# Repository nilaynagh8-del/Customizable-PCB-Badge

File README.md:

# Customizable PCB-Badge
A customizable PCB badge with built in NFC & games!

# Features
- LED Matrix for fun games like flappy bird or pong
- E-ink display module for displaying ID information
- NFC tag for haring info like websites, etc.
- where the NFC tag directs you to can be changed on you're computer through a USB-C connection
- Fun copper and silkscreen art
- 16 broken out GPIO pins
- 16MB of flash storage for the rp2040
- power only needed when playing games or changing the image on the E-ink display
---
# How to Use
| Mode (long-press SW4 to cycle) | What happens |
|---|---|
| 1. **Flappy** | Flappy-bird on the LED grid. SW3 = flap, SW4 = restart. Speeds up as you score. |
| 2. **Pong** | 2-player pong, first to 5. SW3 = left paddle, SW4 = right paddle. |
| 3. **NFC** | Pick one of 3 payloads with SW3 (URL / text / vCard), write it to the ST25DV tag with SW4. Green frame = tag present, red = not detected. Green sweep = write verified OK. |
| 4. **Demo** | Rainbow across the whole grid. |

SW2 toggles the 6 THT LEDs at any time, in any mode – it's wired straight
to GPIO13.

The NFC tag behaves like a normal Type-5 NDEF tag: after a write, tapping it to
a phone opens the URL, shows the text, or offers the contact card.

**Customizing the NFC payloads**

Edit the three strings near the top of `badge-firmware.ino`:

```cpp
static const char *NFC_PAYLOAD_URL   = "https://hackclub.com";
static const char *NFC_PAYLOAD_TEXT  = "Hello to whoever taps this badge!";
static const char *NFC_PAYLOAD_VCARD = "BEGIN:VCARD\nVERSION:3.0\nFN:YOUR NAME...";
```

URI prefixes are auto-detected (`https://`, `http://www.`, `tel:`, `mailto:` …)
and encoded compactly per the NDEF spec. Writes are verified by read-back; the
password session re-opens between attempts if the first write fails. Firmware
size per payload is capped at 254 bytes (TLV short form) but the payload
themselves are clamped to 200 bytes each — plenty for a URL, a message, and a
contact card on the 512-byte ST25DV04K.
# Designing the PCB
the PCB is pretty compact and tightly packed together with many components, which forced me to make this PCB 6 layers. I used 2 GND planes, one on the top layer and another on the bottom. For the NFC antenna I used a plugin to generate me one with copper wire routing to make it part of the PCB itself so it doesn't require an external antenna. here are some photos of the design below.

_Main MCU Components_

_LEDs and buttons for games_

_E-ink Display_

_NFC tag components_

_LED for fun lighting on the front_

_Final PCB Design_

_PCB front and back_

# Software
The software of this device is pretty simple all you have to do is hold the BOOTSEL button on the board and drop the the [Badge-firmware.ino.uf2](https://github.com/nilaynagh8-del/Customizable-PCB-Badge/blob/main/badge-uf2/badge-firmware.ino.uf2) onto the device. You will then be able to upload you're ID and play games etc.

---
# BOM
|#Part       |#Price          |
|------------|----------------|
| **1x [rp2040](https://www.digikey.com/en/products/detail/raspberry-pi/SC0914(13)/14306010)**     | $0.76     |
| **1x [W25Q128JVS](https://www.digikey.com/en/products/detail/winbond-electronics/W25Q128JVSIQ/5803943)** | $5.99   |
| **1x [USB-C 2.0 receptacle](https://www.digikey.com/en/products/detail/adam-tech/USB-C20-S-RA-CS16A-BK-TR/25701126?gclsrc=aw.ds&gad_source=1&gad_campaignid=20678579980&gbraid=0AAAAADrbLlhqkQkBmy0GhcLsBGkQxSWwA&gclid=Cj0KCQjwrvHWBhDKARIsABmp7h3_4yny3H3xYeCTKnwiGQ5gFquwQlYKCZFCwDuY89yn7uL39px1PEEaAn94EALw_wcB)**    | $0.74  |
| **50x[ SK6812MINI LEDS](https://keeb.io/products/sk-6812-mini-e-rgb-leds-12-pack?srsltid=AYCX9vJHpHxhBnKpgdmcaYFWbcuSSWfHne0xMPR1KBHh8PzNO1_xWtn2)**    | $11.98    |
| **1x [ST25DV04K-IER8C3](https://www.digikey.com/en/products/detail/stmicroelectronics/ST25DV04K-IER6T3/6691418?gclsrc=aw.ds&gad_source=1&gad_campaignid=24216345527&gbraid=0AAAAADrbLli4CTTxePQYnJ5C6afwPKjL2&gclid=Cj0KCQjwrvHWBhDKARIsABmp7h1KdPLxHsMZuuaStQSl7R8vMIvJZ-5TIm2zWNzuZK7JSieiJ8zBqwcaAgxCEALw_wcB)**    | $1.10  |
| **6x [5mm THT LED](https://www.digikey.com/en/products/detail/rohm-semiconductor/SLR-56VC3F/636991?gclsrc=aw.ds&gad_source=1&gad_campaignid=20747733577&gbraid=0AAAAADrbLlibUioa_7C1IycEGCDz0hbTg&gclid=Cj0KCQjwrvHWBhDKARIsABmp7h10cfeflSGWLhXNBAp4XJWPd0hMV-nY00NDLkXkriuKhSCe2A7cvd8aAgY_EALw_wcB)**    | $3.30 |
| **3x [PTS645Sx43SMTR92 Switches](https://www.digikey.com/en/products/detail/wec/PTS645SK43SMTR92LFS/27533114?gclsrc=aw.ds&gad_source=4&gad_campaignid=23033451739&gbraid=0AAAAADrbLlh-8VarSu1z8cuQMuamoVxbl&gclid=Cj0KCQjwrvHWBhDKARIsABmp7h1Eo3e9FToyXaLy61q9kBlwUjuhkKtIDu0mgIWiZOV7CFqwBuzqiGIaAisyEALw_wcB)**    | $1.08|
| **1x [KMR2 switch](https://www.digikey.com/en/products/detail/c-k/KMR221G-LFS/550472?gclsrc=aw.ds&gad_source=1&gad_campaignid=20243136172&gbraid=0AAAAADrbLlj0U90TogABbZu38P156Ls3i&gclid=Cj0KCQjwrvHWBhDKARIsABmp7h1JYl6i5VjO5_h80ofNfqxeWJDCjkMDnMpPE0zijLod7d3QZ9AqAecaAiA4EALw_wcB)**    | $0.67 |
| **14x[ 0402 0.1uf capacitors](https://www.digikey.com/en/products/detail/murata-electronics/GRM155C81E104KA12D/6605993?gclsrc=aw.ds&gad_source=4&gad_campaignid=20509818233&gbraid=0AAAAADrbLlis9pHS9r0m2ZhlQP6IInvQA&gclid=Cj0KCQjwrvHWBhDKARIsABmp7h07aUFT4WDWhllQ61V_xpzCK5QXNSUuiS_rN4leZ1_dai8NjVI8rQsaAgjsEALw_wcB)**    | $1.40    |
| **3x [0603 10uf capacitors](https://www.digikey.com/en/products/detail/murata-electronics/GRT188R60J106ME13J/13904886?gclsrc=aw.ds&gad_source=1&gad_campaignid=20509818233&gbraid=0AAAAADrbLlhW4hUYZwqaRXxXOI1TvvnLC&gclid=Cj0KCQjwrvHWBhDKARIsABmp7h1m43mU9iI4nKG-fnOtnU_kfMY8bhoRzj5BhlG1TujyhKJdcvszKPgaAnMzEALw_wcB)**    | $0.63 |
| **4x [0402 15pf  capacitors](https://www.digikey.com/en/products/detail/yageo/CC0402FRNPO9BN150/5195051)**    | $0.52    |
| **1x [NCP1117ST33T3G](https://www.digikey.com/en/products/detail/onsemi/NCP1117ST33T3G/1749063)**    | $0.65    |
| **2x [5.1k 0402 resistors](https://www.digikey.com/en/products/detail/yageo/RC0402FR-075K1L/726624)**    | $0.20    |
| **2x [27 ohm 0402 resistors](https://www.digikey.com/en/products/detail/yageo/RC0402FR-0727RL/5280946)**    | $0.20    |
| **2x [1k  0402 resistors](https://www.digikey.com/en/products/detail/yageo/RC0402FR-071KL/726513)**    | $0.20    |
| **1x [10k  0402 resistors](https://www.digikey.com/en/products/detail/vishay-dale/RCA040210K0FKED/4946751)**    | $0.11 |
| **2x [4.7k  0402 resistors](https://www.digikey.com/en/products/detail/yageo/RC0402JR-074K7L/726477)**    | $0.10 |
| **1x [470 ohm  0402 resistors](https://www.digikey.com/en/products/detail/yageo/RC0402FR-07470RP/4935284)**    | $0.11 |
| **1x [E-ink Display]([https://www.digikey.com/en/products/detail/yageo/RC0402FR-07470RP/4935284](https://www.amazon.com/2-13inch-Display-HAT-Two-Color-Raspberry/dp/B07Z1WYRQH/ref=sr_1_11?dib=eyJ2IjoiMSJ9.gn6VLudgU0EyGmCtn6ouiN-En84h8hGdmjGuK1-66Xws_QcTkqImKZ7qe8NUiArwhwJk9JiOutgNeIz5cPmB0ZbkMG4yFjYDLpp9DKV0toxfU2H8bp0QUR760J-i1QKpJPyA7FF0PKqdo7Qt2GiVY_zAQcLqV49bpBDsulBlm3EtA--w29KZabezZMWkaSrQsFDFI53NmnQb6Gi7EZZHmbqM53_gEwxUkAk3kj63XW4.dg_95URBlxNDf7plGtIUSDxYDGLFnQ1UMweHCZRH_n8&dib_tag=se&keywords=e-ink+display&qid=1792900939&sr=8-11))**    | $23.03 |
| **Total Price of Parts (excluding PCB)**  | $52.77 |

# Disclaimers & Credits
This project is open source. If anything you make out of this does not work or has any issues, I sincerely apologize, but at the end of the day that's on you. Big shout out to Hack Club for giving me the opportunity to make this project. I would also like to thank **Kai Pereira**, as my project is heavily inspired his PCB badge in many ways.

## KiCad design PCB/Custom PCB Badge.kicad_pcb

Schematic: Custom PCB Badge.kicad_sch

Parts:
C1, C2, C3, C4, C5, C6, C7, C8, C9, C10, C11, C12, C17: 0.1uf; C_0402_1005Metric_Pad0.74x0.62mm_HandSolder
C13, C14, C18: 10uf; C_0603_1608Metric_Pad1.08x0.95mm_HandSolder
C15, C16: 15pf; C_0402_1005Metric_Pad0.74x0.62mm_HandSolder
J1: USB_C_Receptacle_USB2.0_14P; USB_C_Receptacle_HRO_TYPE-C-31-M-12
J3: Conn_01x15_MountingPin; PinHeader_1x15_P2.54mm_Vertical
J8: Conn_01x11_MountingPin; PinHeader_1x11_P2.54mm_Vertical
R1: 5.1K; R_0402_1005Metric_Pad0.72x0.64mm_HandSolder
R2: 5.1k; R_0402_1005Metric_Pad0.72x0.64mm_HandSolder
R3, R4: 27; R_0402_1005Metric_Pad0.72x0.64mm_HandSolder
R5, R6: 1k; R_0402_1005Metric_Pad0.72x0.64mm_HandSolder
R7: 10k; R_0402_1005Metric_Pad0.72x0.64mm_HandSolder
SW1: SW_Push; SW_Push_1P1T_NO_CK_KMR2
U1: RP2040; QFN-56-1EP_7x7mm_P0.4mm_EP3.2x3.2mm
U2: NCP1117-3.3_SOT223; SOT-223-3_TabPin2
U3: W25Q128JVS; SOIC-8_5.3x5.3mm_P1.27mm
Y1: 12mhz; Crystal_SMD_3225-4Pin_3.2x2.5mm_HandSoldering

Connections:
+1V1: C10.1, C11.1, C12.1, U1.43 (ADC_AVDD), U1.48 (USB_VDD)
+3V3: C1.1, C2.1, C3.1, C4.1, C5.1, C6.1, C7.1, C8.1, C9.1, C14.1, C17.1, J3.5, J8.5, R7.1, U1.1 (IOVDD), U1.10 (IOVDD), U1.22 (IOVDD), U1.23 (DVDD), U1.33 (IOVDD), U1.42 (IOVDD), U1.44 (VREG_VIN), U1.45 (VREG_VOUT), U1.49 (IOVDD), U1.50 (DVDD), U2.2 (VO), U3.8 (VCC); also elsewhere on the board
+5V: C13.1, C18.1, J1.A4 (VBUS), J1.A9 (VBUS), J1.B4 (VBUS), J1.B9 (VBUS), J3.1, J8.1, U2.3 (VI)
/d+: J1.A6 (D+), J1.B6 (D+), R3.1
/d-: J1.A7 (D-), J1.B7 (D-), R4.1
/xin: C16.2, U1.20 (XIN), Y1.3
/xout: R5.2, U1.21 (XOUT)
GND: C1.2, C2.2, C3.2, C4.2, C5.2, C6.2, C7.2, C8.2, C9.2, C10.2, C11.2, C12.2, C13.2, C14.2, C15.1, C16.1, C17.2, C18.2, J1.A1 (GND), J1.A12 (GND), J1.B1 (GND), J1.B12 (GND), J1.SH (SHIELD), J3.3, J3.8, J3.13, J8.3, J8.8, J8.10, R1.2, R2.1, SW1.1, U1.19 (TESTEN), U1.57 (GND), U2.1 (GND), U3.4 (GND), Y1.2 (G), Y1.4 (G); also elsewhere on the board
GPIO0: J3.2, U1.2 (GPIO0)
GPIO1: J3.4, U1.3 (GPIO1)
GPIO2: J3.6, U1.4 (GPIO2)
GPIO3: J3.7, U1.5 (GPIO3)
GPIO4: J3.9, U1.6 (GPIO4)
GPIO5: J3.10, U1.7 (GPIO5)
GPIO6: J3.11, U1.8 (GPIO6)
GPIO7: J3.12, U1.9 (GPIO7)
GPIO8: J3.14, U1.11 (GPIO8)
GPIO9: J3.15, U1.12 (GPIO9)
GPIO10: U1.13 (GPIO10); also elsewhere on the board
GPIO11: U1.14 (GPIO11); also elsewhere on the board
GPIO12: U1.15 (GPIO12); also elsewhere on the board
GPIO13: U1.16 (GPIO13); also elsewhere on the board
GPIO14: J8.4, U1.17 (GPIO14)
GPIO15: J8.6, U1.18 (GPIO15)
GPIO16: J8.7, U1.27 (GPIO16)
GPIO17: J8.9, U1.28 (GPIO17)
GPIO18: J8.11, U1.29 (GPIO18)
GPIO19: J8.2, U1.30 (GPIO19)
GPIO20: U1.31 (GPIO20); also elsewhere on the board
GPIO21: U1.32 (GPIO21); also elsewhere on the board
GPIO22: U1.34 (GPIO22); also elsewhere on the board
GPIO23: U1.35 (GPIO23); also elsewhere on the board
GPIO24: U1.36 (GPIO24); also elsewhere on the board
GPIO25: U1.37 (GPIO25); also elsewhere on the board
GPIO26: U1.38 (GPIO26/ADC0); also elsewhere on the board
GPIO27: U1.39 (GPIO27/ADC1); also elsewhere on the board
GPIO28: U1.40 (GPIO28/ADC2); also elsewhere on the board
GPIO29: U1.41 (GPIO29/ADC3); also elsewhere on the board
unnamed: C15.2, R5.1, Y1.1
unnamed: J1.A5 (CC1), R1.1
unnamed: J1.B5 (CC2), R2.2
unnamed: R6.1, SW1.2
unnamed: R3.2, U1.46 (USB_DM)
unnamed: R4.2, U1.47 (USB_DP)
QSPISS: R6.2, R7.2, U1.56 (~QSPI_SS), U3.1 (~CS)
QSPI_SCLK: U1.52 (QSPI_SCLK), U3.6 (CLK)
QSPI_SD0: U1.53 (QSPI_SD0), U3.5 (DI/IO_{0})
QSPI_SD1: U1.55 (QSPI_SD1), U3.2 (DO/IO_{1})
QSPI_SD2: U1.54 (QSPI_SD2), U3.3 (~WP/IO_{2})
QSPI_SD3: U1.51 (QSPI_SD3), U3.7 (~HOLD/~RESET/IO_{3})
RUN: U1.26 (RUN)

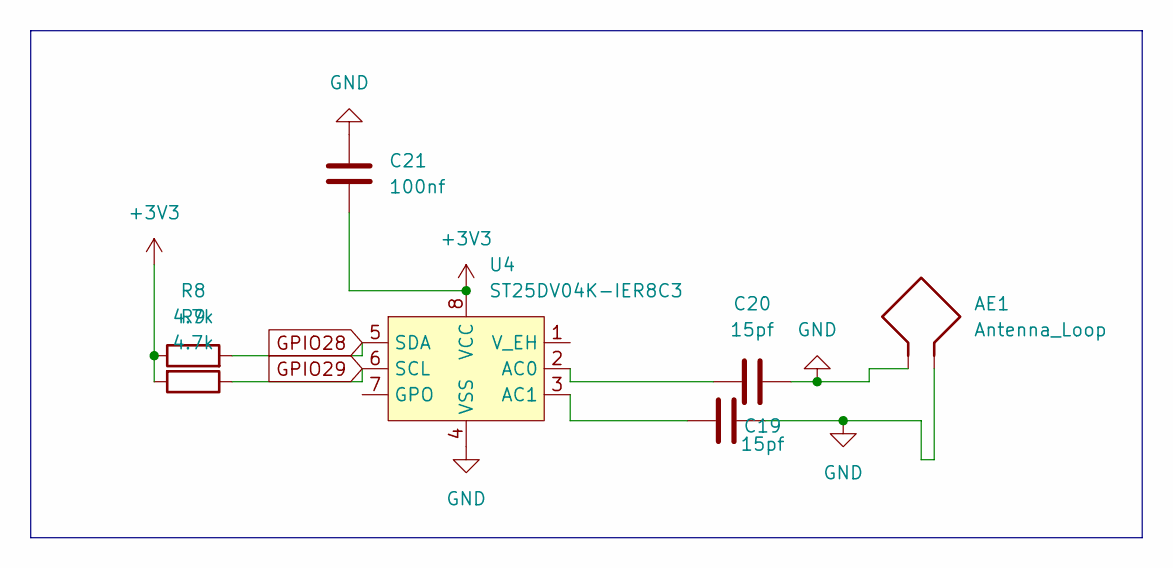
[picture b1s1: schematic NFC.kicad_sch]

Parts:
AE1: Antenna_Loop; PinHeader_1x02_P2.54mm_Vertical_SMD_Pin1Left
C19, C20: 15pf; C_0402_1005Metric_Pad0.74x0.62mm_HandSolder
C21: 100nf; C_0402_1005Metric_Pad0.74x0.62mm_HandSolder
R8, R9: 4.7k; R_0402_1005Metric_Pad0.72x0.64mm_HandSolder
U4: ST25DV04K-IER8C3; DFN-8-1EP_3x2mm_P0.5mm_EP1.36x1.46mm

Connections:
+3V3: C21.1, R8.1, R9.2, U4.8 (VCC); also elsewhere on the board
GND: AE1.1, AE1.2, C19.2, C20.2, C21.2, U4.4 (VSS); also elsewhere on the board
GPIO28: R8.2, U4.5 (SDA); also elsewhere on the board
GPIO29: R9.1, U4.6 (SCL); also elsewhere on the board
unnamed: C20.1, U4.2 (AC0)
unnamed: C19.1, U4.3 (AC1)

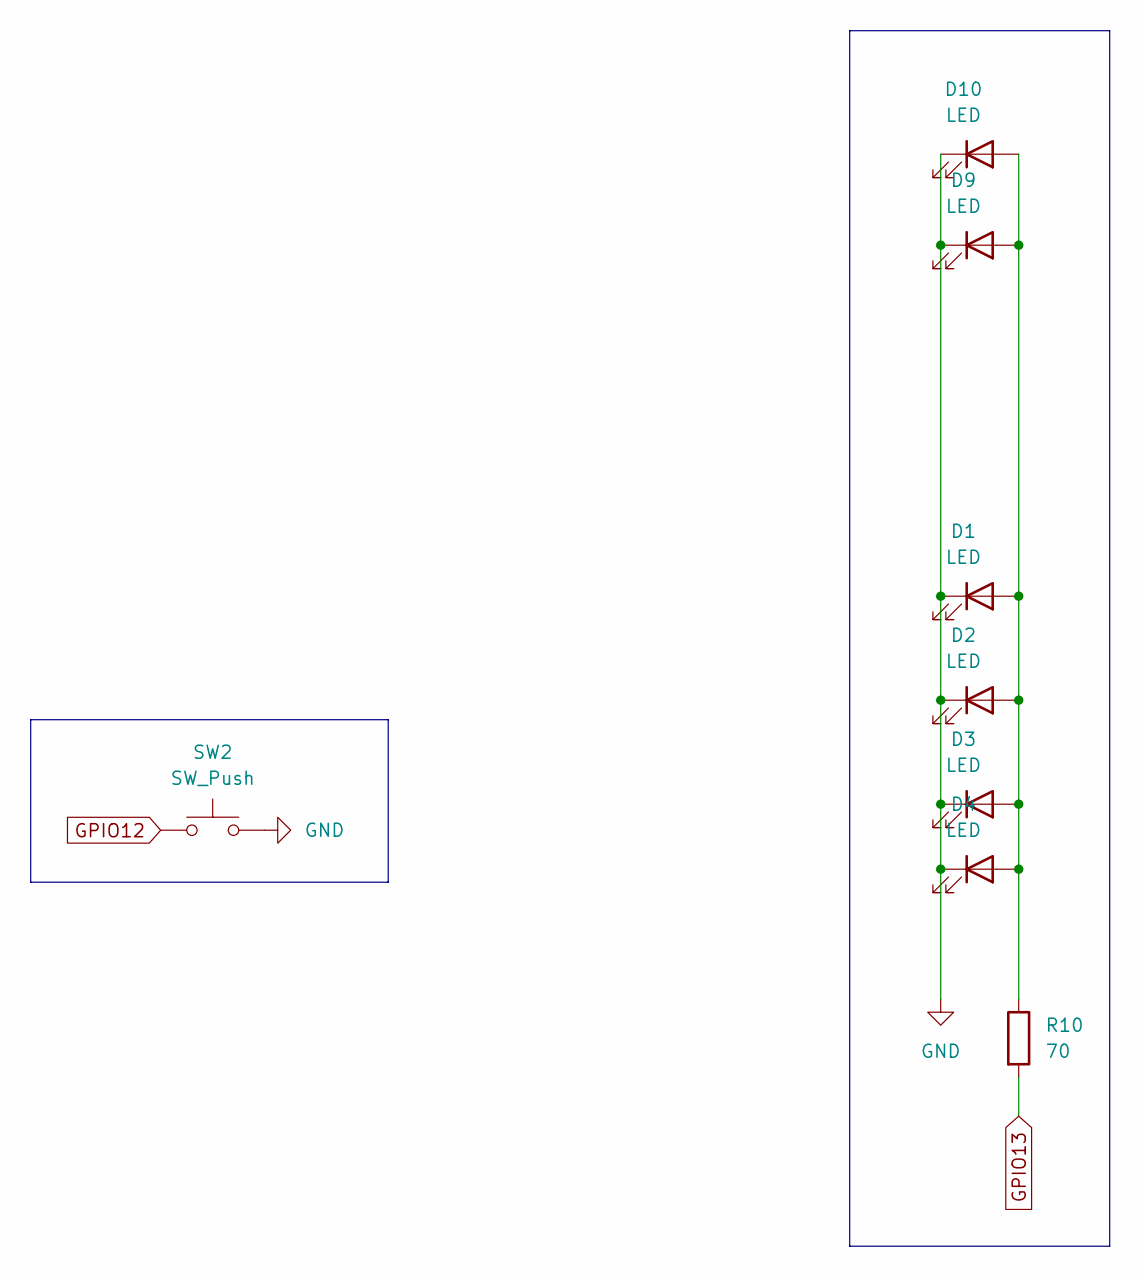
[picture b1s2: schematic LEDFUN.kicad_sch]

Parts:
D1, D2, D3, D4, D9, D10: LED; LED_D5.0mm
R10: 70; R_0402_1005Metric_Pad0.72x0.64mm_HandSolder
SW2: SW_Push; SW_SPST_PTS645Sx43SMTR92

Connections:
GND: D1.1 (K), D2.1 (K), D3.1 (K), D4.1 (K), D9.1 (K), D10.1 (K), SW2.2; also elsewhere on the board
GPIO12: SW2.1; also elsewhere on the board
GPIO13: R10.2; also elsewhere on the board
unnamed: D1.2 (A), D2.2 (A), D3.2 (A), D4.2 (A), D9.2 (A), D10.2 (A), R10.1

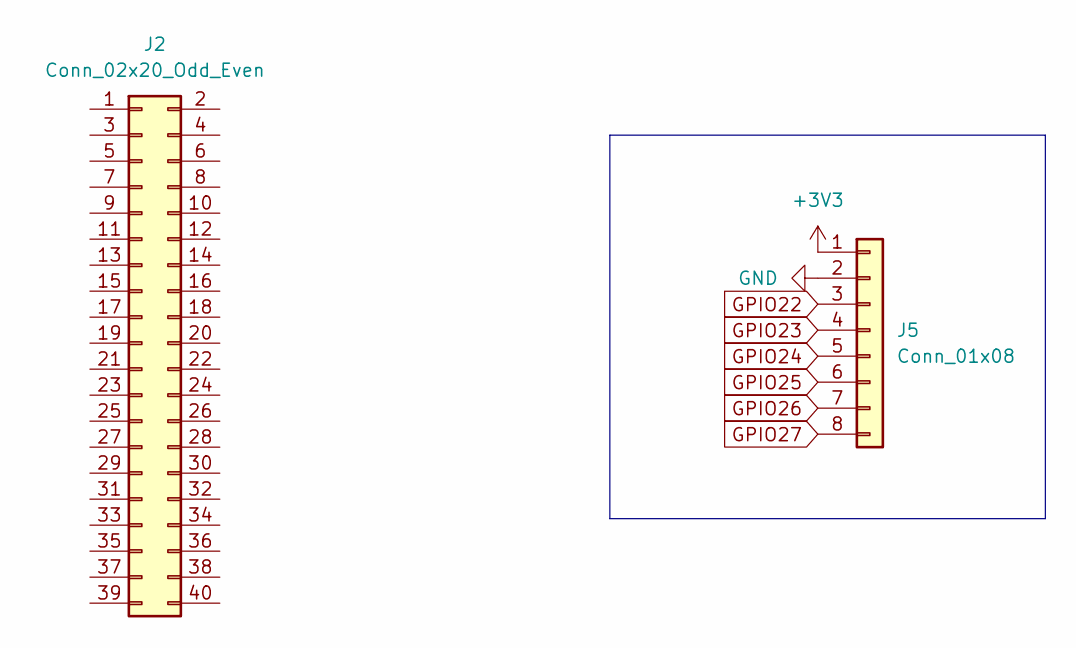
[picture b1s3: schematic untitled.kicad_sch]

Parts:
J2: Conn_02x20_Odd_Even; PinHeader_2x20_P2.54mm_Vertical
J5: Conn_01x08; PinHeader_1x08_P2.54mm_Vertical

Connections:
+3V3: J5.1; also elsewhere on the board
GND: J5.2; also elsewhere on the board
GPIO22: J5.3; also elsewhere on the board
GPIO23: J5.4; also elsewhere on the board
GPIO24: J5.5; also elsewhere on the board
GPIO25: J5.6; also elsewhere on the board
GPIO26: J5.7; also elsewhere on the board
GPIO27: J5.8; also elsewhere on the board

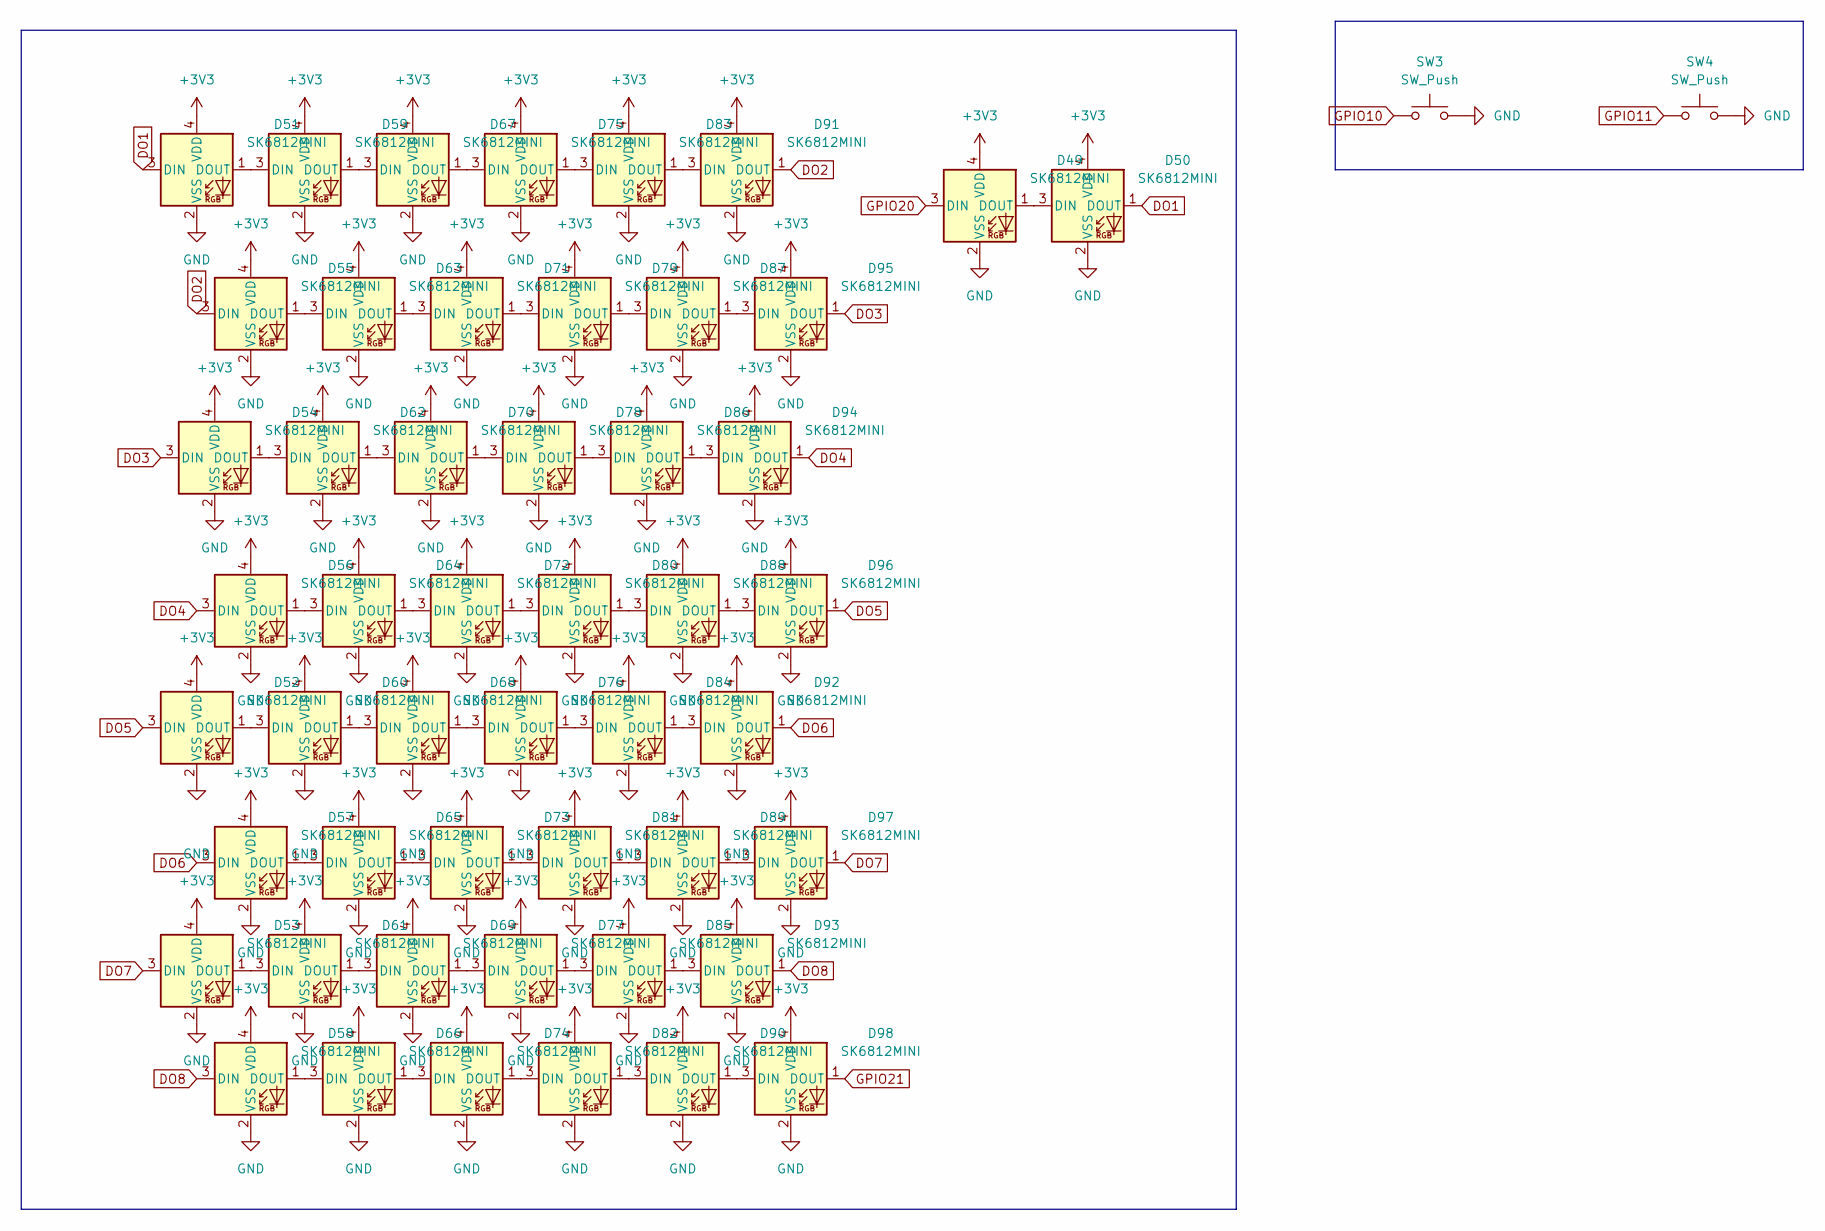
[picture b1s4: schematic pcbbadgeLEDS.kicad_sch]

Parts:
D49, D50, D51, D52, D53, D54, D55, D56, D57, D58, D59, D60, D61, D62, D63, D64, D65, D66, D67, D68, D69, D70, D71, D72, D73, D74, D75, D76, D77, D78, D79, D80, D81, D82, D83, D84, D85, D86, D87, D88, D89, D90, D91, D92, D93, D94, D95, D96, D97, D98: SK6812MINI; LED_SK6812MINI_PLCC4_3.5x3.5mm_P1.75mm
SW3, SW4: SW_Push; SW_SPST_PTS645Sx43SMTR92

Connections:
+3V3: D49.4 (VDD), D50.4 (VDD), D51.4 (VDD), D52.4 (VDD), D53.4 (VDD), D54.4 (VDD), D55.4 (VDD), D56.4 (VDD), D57.4 (VDD), D58.4 (VDD), D59.4 (VDD), D60.4 (VDD), D61.4 (VDD), D62.4 (VDD), D63.4 (VDD), D64.4 (VDD), D65.4 (VDD), D66.4 (VDD), D67.4 (VDD), D68.4 (VDD), D69.4 (VDD), D70.4 (VDD), D71.4 (VDD), D72.4 (VDD), D73.4 (VDD), D74.4 (VDD), D75.4 (VDD), D76.4 (VDD), D77.4 (VDD), D78.4 (VDD), D79.4 (VDD), D80.4 (VDD), D81.4 (VDD), D82.4 (VDD), D83.4 (VDD), D84.4 (VDD), D85.4 (VDD), D86.4 (VDD), D87.4 (VDD), D88.4 (VDD), D89.4 (VDD), D90.4 (VDD), D91.4 (VDD), D92.4 (VDD), D93.4 (VDD), D94.4 (VDD), D95.4 (VDD), D96.4 (VDD), D97.4 (VDD), D98.4 (VDD); also elsewhere on the board
DO1: D50.1 (DOUT), D51.3 (DIN)
DO2: D55.3 (DIN), D91.1 (DOUT)
DO3: D54.3 (DIN), D95.1 (DOUT)
DO4: D56.3 (DIN), D94.1 (DOUT)
DO5: D52.3 (DIN), D96.1 (DOUT)
DO6: D57.3 (DIN), D92.1 (DOUT)
DO7: D53.3 (DIN), D97.1 (DOUT)
DO8: D58.3 (DIN), D93.1 (DOUT)
GND: D49.2 (VSS), D50.2 (VSS), D51.2 (VSS), D52.2 (VSS), D53.2 (VSS), D54.2 (VSS), D55.2 (VSS), D56.2 (VSS), D57.2 (VSS), D58.2 (VSS), D59.2 (VSS), D60.2 (VSS), D61.2 (VSS), D62.2 (VSS), D63.2 (VSS), D64.2 (VSS), D65.2 (VSS), D66.2 (VSS), D67.2 (VSS), D68.2 (VSS), D69.2 (VSS), D70.2 (VSS), D71.2 (VSS), D72.2 (VSS), D73.2 (VSS), D74.2 (VSS), D75.2 (VSS), D76.2 (VSS), D77.2 (VSS), D78.2 (VSS), D79.2 (VSS), D80.2 (VSS), D81.2 (VSS), D82.2 (VSS), D83.2 (VSS), D84.2 (VSS), D85.2 (VSS), D86.2 (VSS), D87.2 (VSS), D88.2 (VSS), D89.2 (VSS), D90.2 (VSS), D91.2 (VSS), D92.2 (VSS), D93.2 (VSS), D94.2 (VSS), D95.2 (VSS), D96.2 (VSS), D97.2 (VSS), D98.2 (VSS), SW3.2, SW4.2; also elsewhere on the board
GPIO10: SW3.1; also elsewhere on the board
GPIO11: SW4.1; also elsewhere on the board
GPIO20: D49.3 (DIN); also elsewhere on the board
GPIO21: D98.1 (DOUT); also elsewhere on the board
unnamed: D49.1 (DOUT), D50.3 (DIN)
unnamed: D51.1 (DOUT), D59.3 (DIN)
unnamed: D52.1 (DOUT), D60.3 (DIN)
unnamed: D53.1 (DOUT), D61.3 (DIN)
unnamed: D54.1 (DOUT), D62.3 (DIN)
unnamed: D55.1 (DOUT), D63.3 (DIN)
unnamed: D56.1 (DOUT), D64.3 (DIN)
unnamed: D57.1 (DOUT), D65.3 (DIN)
unnamed: D58.1 (DOUT), D66.3 (DIN)
unnamed: D59.1 (DOUT), D67.3 (DIN)
unnamed: D60.1 (DOUT), D68.3 (DIN)
unnamed: D61.1 (DOUT), D69.3 (DIN)
unnamed: D62.1 (DOUT), D70.3 (DIN)
unnamed: D63.1 (DOUT), D71.3 (DIN)
unnamed: D64.1 (DOUT), D72.3 (DIN)
unnamed: D65.1 (DOUT), D73.3 (DIN)
unnamed: D66.1 (DOUT), D74.3 (DIN)
unnamed: D67.1 (DOUT), D75.3 (DIN)
unnamed: D68.1 (DOUT), D76.3 (DIN)
unnamed: D69.1 (DOUT), D77.3 (DIN)
unnamed: D70.1 (DOUT), D78.3 (DIN)
unnamed: D71.1 (DOUT), D79.3 (DIN)
unnamed: D72.1 (DOUT), D80.3 (DIN)
unnamed: D73.1 (DOUT), D81.3 (DIN)
unnamed: D74.1 (DOUT), D82.3 (DIN)
unnamed: D75.1 (DOUT), D83.3 (DIN)
unnamed: D76.1 (DOUT), D84.3 (DIN)
unnamed: D77.1 (DOUT), D85.3 (DIN)
unnamed: D78.1 (DOUT), D86.3 (DIN)
unnamed: D79.1 (DOUT), D87.3 (DIN)
unnamed: D80.1 (DOUT), D88.3 (DIN)
unnamed: D81.1 (DOUT), D89.3 (DIN)
unnamed: D82.1 (DOUT), D90.3 (DIN)
unnamed: D83.1 (DOUT), D91.3 (DIN)
unnamed: D84.1 (DOUT), D92.3 (DIN)
unnamed: D85.1 (DOUT), D93.3 (DIN)
unnamed: D86.1 (DOUT), D94.3 (DIN)
unnamed: D87.1 (DOUT), D95.3 (DIN)
unnamed: D88.1 (DOUT), D96.3 (DIN)
unnamed: D89.1 (DOUT), D97.3 (DIN)
unnamed: D90.1 (DOUT), D98.3 (DIN)

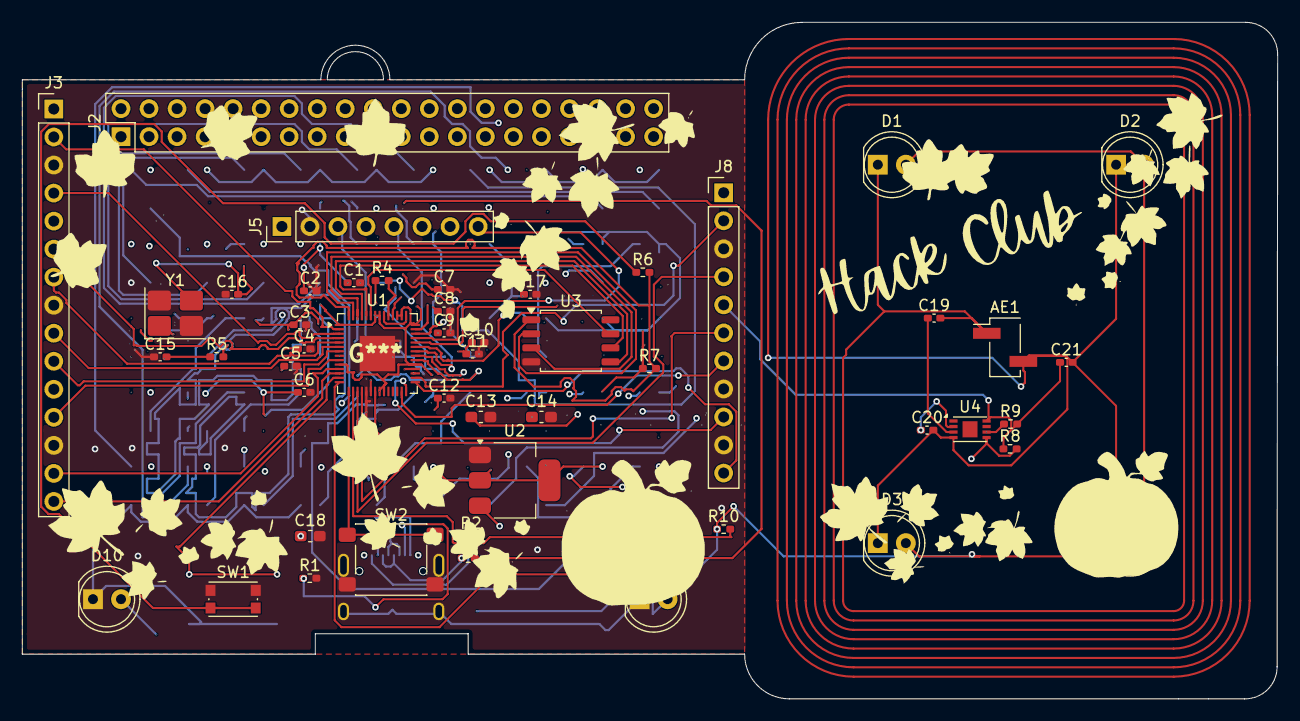
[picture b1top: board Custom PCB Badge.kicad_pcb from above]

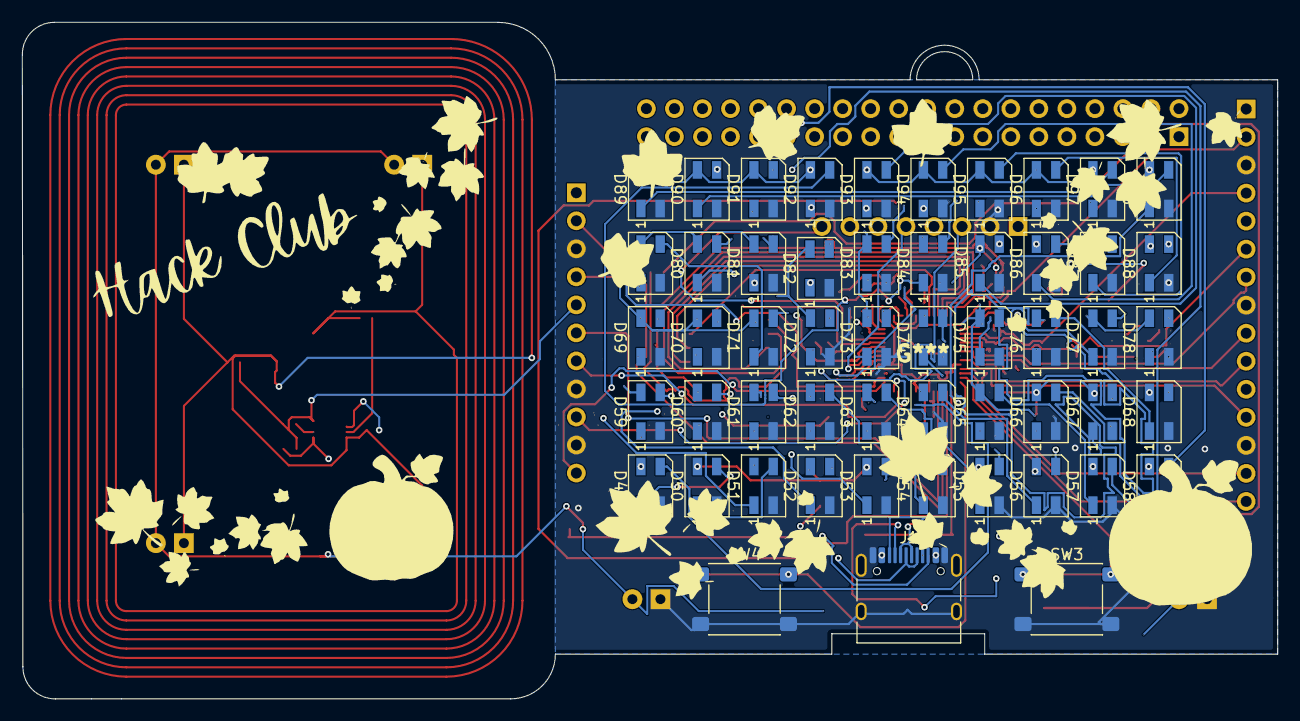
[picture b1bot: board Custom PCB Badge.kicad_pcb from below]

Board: 6 copper layers, 113.7 x 61.3 mm, 102 parts (53 on the bottom side), 102 nets.

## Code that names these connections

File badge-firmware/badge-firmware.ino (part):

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//  Custom PCB Badge firmware  —  RP2040-QFN-56 + W25Q128 + 12MHz XIN + USB-C
//
//  Hardware map (extracted from the KiCad netlist):
//    * 50x SK6812MINI (on B.Cu) in a 10 x 5 grid, data chain starts at GPIO20
//      (the chain's last pixel DOUT loops back to GPIO21 — unused here)
//    * SW3 (game button A)  -> GPIO10  (pressed = LOW, INPUT_PULLUP)
//    * SW4 (game button B)  -> GPIO11  (pressed = LOW, INPUT_PULLUP)
//    * SW2 (THT LED toggle) -> GPIO12  (pressed = LOW, INPUT_PULLUP)
//    * D1..D10 THT LED row via shared 70R    -> GPIO13 (HIGH = all 10 ON)
//    * SW1 = BOOTSEL button — handled by the chip ROM, never used by code
//    * ST25DV04K NFC: SDA = GPIO28, SCL = GPIO29 (external 4k7 pullups)
//
//  Modes (cycle with long-press SW4, 0.8 s):
//    0. Flappy  — SW3 to flap, SW4 to restart
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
